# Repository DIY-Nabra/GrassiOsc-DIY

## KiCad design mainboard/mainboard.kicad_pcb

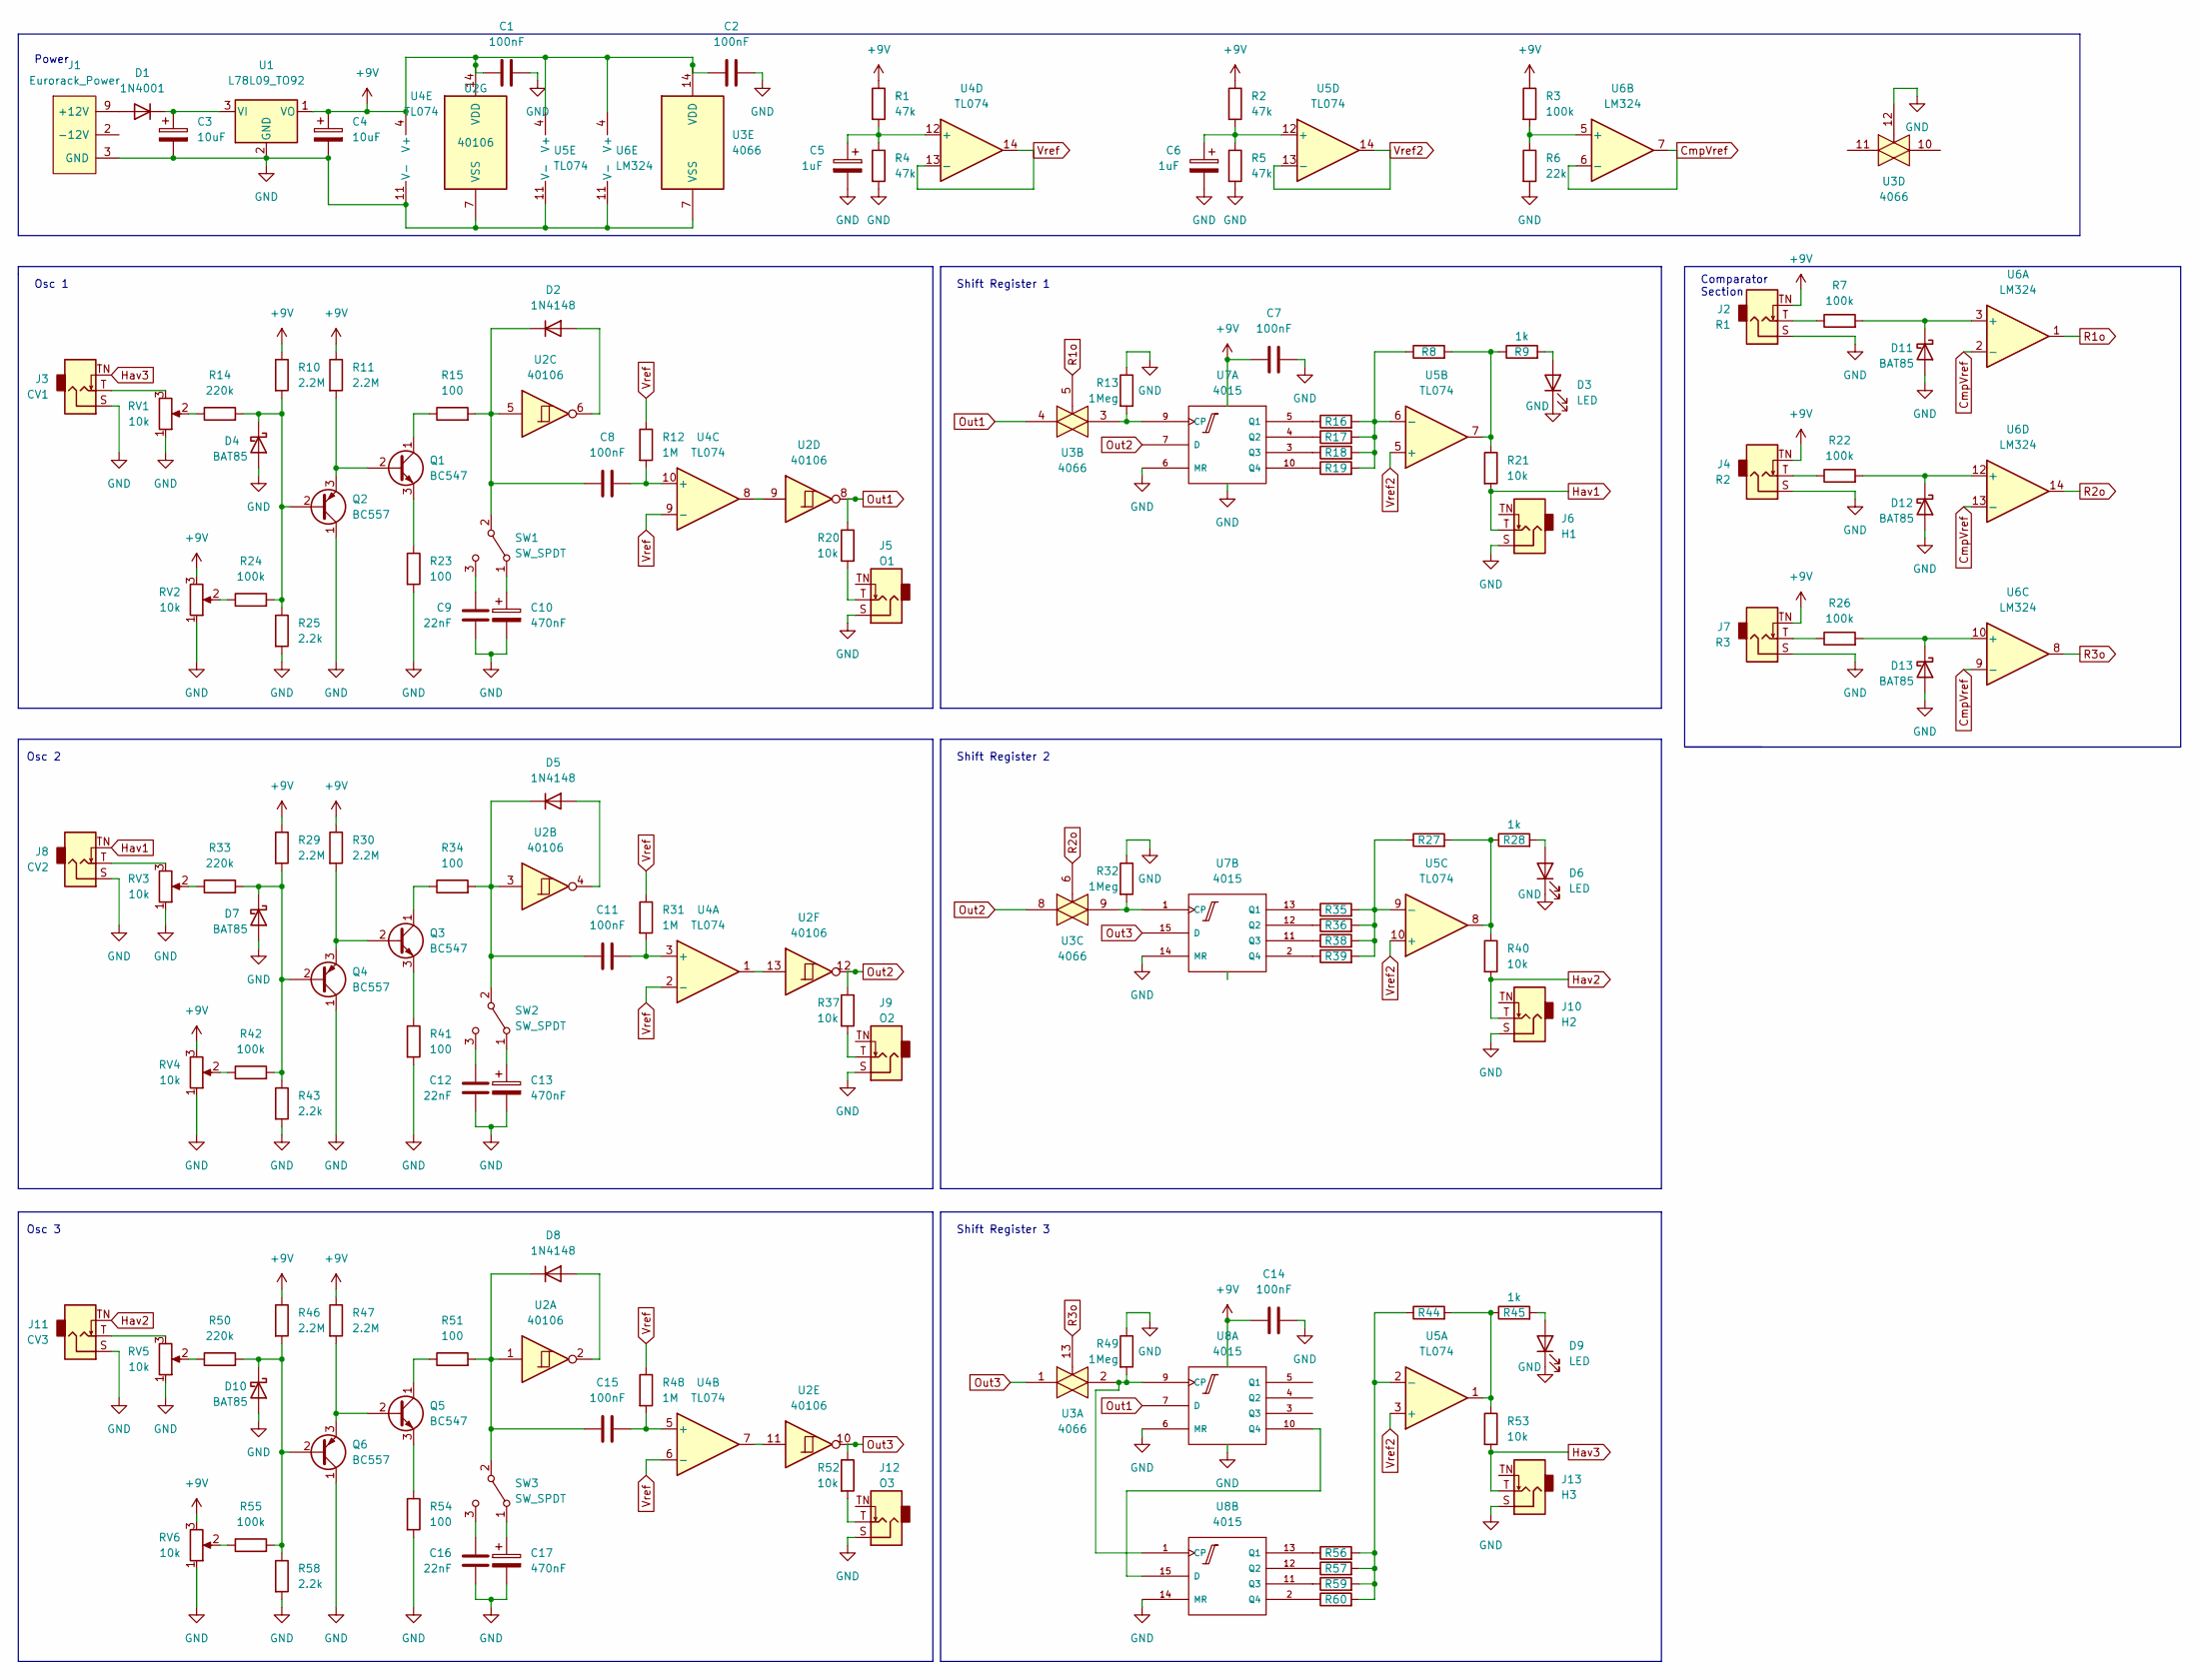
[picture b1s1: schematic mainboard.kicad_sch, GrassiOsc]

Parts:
C1, C2, C7, C14: 100nF; C_Disc_D5.0mm_W2.5mm_P2.50mm
C3, C4: 10uF; CP_Radial_D5.0mm_P2.50mm
C5, C6: 1uF; C_Disc_D3.8mm_W2.6mm_P2.50mm
C8, C11, C15: 100nF; C_Rect_L7.0mm_W2.5mm_P5.00mm
C9, C12, C16: 22nF; C_Disc_D5.0mm_W2.5mm_P2.50mm
C10, C13, C17: 470nF; CP_Radial_D5.0mm_P2.50mm
D1: 1N4001; D_DO-41_SOD81_P10.16mm_Horizontal
D2, D5, D8: 1N4148; D_DO-35_SOD27_P7.62mm_Horizontal
D3, D6, D9: LED; LED_D3.0mm
D4, D7, D10, D11, D12, D13: BAT85; D_DO-35_SOD27_P7.62mm_Horizontal
J1: Eurorack_Power; Eurorack_Power_2x5_Shrouded; mpn 302-S101
J2: R1; AudioJack_WQP518MA
J3: CV1; AudioJack_WQP518MA
J4: R2; AudioJack_WQP518MA
J5: O1; AudioJack_WQP518MA
J6: H1; AudioJack_WQP518MA
J7: R3; AudioJack_WQP518MA
J8: CV2; AudioJack_WQP518MA
J9: O2; AudioJack_WQP518MA
J10: H2; AudioJack_WQP518MA
J11: CV3; AudioJack_WQP518MA
J12: O3; AudioJack_WQP518MA
J13: H3; AudioJack_WQP518MA
Q1, Q3, Q5: BC547; TO-92_Inline
Q2, Q4, Q6: BC557; TO-92_Inline
R1, R2, R4, R5: 47k; R_Axial_DIN0204_L3.6mm_D1.6mm_P7.62mm_Horizontal
R3, R7, R22, R24, R26, R42, R55: 100k; R_Axial_DIN0204_L3.6mm_D1.6mm_P7.62mm_Horizontal
R6: 22k; R_Axial_DIN0204_L3.6mm_D1.6mm_P7.62mm_Horizontal
R8, R16, R17, R18, R19, R27, R35, R36, R38, R39, R44, R56, R57, R59, R60: R; R_Axial_DIN0204_L3.6mm_D1.6mm_P7.62mm_Horizontal
R9, R28, R45: 1k; R_Axial_DIN0204_L3.6mm_D1.6mm_P7.62mm_Horizontal
R10, R11, R29, R30, R46, R47: 2.2M; R_Axial_DIN0204_L3.6mm_D1.6mm_P7.62mm_Horizontal
R12, R31, R48: 1M; R_Axial_DIN0204_L3.6mm_D1.6mm_P7.62mm_Horizontal
R13, R32, R49: 1Meg; R_Axial_DIN0204_L3.6mm_D1.6mm_P7.62mm_Horizontal
R14, R33, R50: 220k; R_Axial_DIN0204_L3.6mm_D1.6mm_P7.62mm_Horizontal
R15, R23, R34, R41, R51, R54: 100; R_Axial_DIN0204_L3.6mm_D1.6mm_P7.62mm_Horizontal
R20, R21, R37, R40, R52, R53: 10k; R_Axial_DIN0204_L3.6mm_D1.6mm_P7.62mm_Horizontal
R25, R43, R58: 2.2k; R_Axial_DIN0204_L3.6mm_D1.6mm_P7.62mm_Horizontal
RV1, RV2, RV3, RV4, RV5, RV6: 10k; Potentiometer_Alpha_R0904N
SW1, SW2, SW3: SW_SPDT; Miniature_Switch_SPDT_2.54MM
U1: L78L09_TO92; TO-92_Inline
U2: 40106; DIP-14_W7.62mm_Socket
U3: 4066; DIP-14_W7.62mm_Socket
U4, U5: TL074; DIP-14_W7.62mm_Socket
U6: LM324; DIP-14_W7.62mm_Socket
U7, U8: 4015; DIP-16_W7.62mm_Socket

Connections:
+9V: C1.1, C2.1, C4.1, C7.1, C14.1, J2.TN, J4.TN, J7.TN, R1.1, R2.1, R3.1, R10.1, R11.1, R29.1, R30.1, R46.1, R47.1, RV2.3, RV4.3, RV6.3, U1.1 (VO), U2.14 (VDD), U3.14 (VDD), U4.4 (V+), U5.4 (V+), U6.4 (V+), U7.16 (Vdd), U8.16 (Vdd)
CmpVref: U6.2 (-), U6.6 (-), U6.7, U6.9 (-), U6.13 (-)
GND: C1.2, C2.2, C3.2, C4.2, C5.2, C6.2, C7.2, C9.1, C10.2, C12.1, C13.2, C14.2, C16.1, C17.2, D3.1 (K), D4.2 (A), D6.1 (K), D7.2 (A), D9.1 (K), D10.2 (A), D11.2 (A), D12.2 (A), D13.2 (A), J1.3 (GND), J1.4 (GND), J1.5 (GND), J1.6 (GND), J1.7 (GND), J1.8 (GND), J2.S, J3.S, J4.S, J5.S, J6.S, J7.S, J8.S, J9.S, J10.S, J11.S, J12.S, J13.S, Q2.1 (C), Q4.1 (C), Q6.1 (C), R4.2, R5.2, R6.2, R13.1, R23.2, R25.2, R32.1, R41.2, R43.2, R49.1, R54.2, R58.2, RV1.1, RV2.1, RV3.1, RV4.1, RV5.1, RV6.1, U1.2 (GND), U2.7 (VSS), U3.7 (VSS), U3.12, U4.11 (V-), U5.11 (V-), U6.11 (V-), U7.6 (MR), U7.8 (Vss), U7.14 (MR), U8.6 (MR), U8.8 (Vss), U8.14 (MR)
Hav1: J6.T, J8.TN, R21.2
Hav2: J10.T, J11.TN, R40.2
Hav3: J3.TN, J13.T, R53.2
unnamed: C3.1, D1.1 (K), U1.3 (VI)
unnamed: C5.1, R1.2, R4.1, U4.12 (+)
unnamed: C6.1, R2.2, R5.1, U5.12 (+)
unnamed: C8.1, D2.1 (K), R15.2, SW1.2 (B), U2.5
unnamed: C8.2, R12.2, U4.10 (+)
unnamed: C9.2, SW1.3 (C)
unnamed: C10.1, SW1.1 (A)
unnamed: C11.1, D5.1 (K), R34.2, SW2.2 (B), U2.3
unnamed: C11.2, R31.2, U4.3 (+)
unnamed: C12.2, SW2.3 (C)
unnamed: C13.1, SW2.1 (A)
unnamed: C15.1, D8.1 (K), R51.2, SW3.2 (B), U2.1
unnamed: C15.2, R48.2, U4.5 (+)
unnamed: C16.2, SW3.3 (C)
unnamed: C17.1, SW3.1 (A)
unnamed: D1.2 (A), J1.9 (+12V), J1.10 (+12V)
unnamed: D2.2 (A), U2.6
unnamed: D3.2 (A), R9.2
unnamed: D4.1 (K), Q2.2 (B), R10.2, R14.2, R24.2, R25.1
unnamed: D5.2 (A), U2.4
unnamed: D6.2 (A), R28.2
unnamed: D7.1 (K), Q4.2 (B), R29.2, R33.2, R42.2, R43.1
unnamed: D8.2 (A), U2.2
unnamed: D9.2 (A), R45.2
unnamed: D10.1 (K), Q6.2 (B), R46.2, R50.2, R55.2, R58.1
unnamed: D11.1 (K), R7.2, U6.3 (+)
unnamed: D12.1 (K), R22.2, U6.12 (+)
unnamed: D13.1 (K), R26.2, U6.10 (+)
unnamed: J1.1 (-12V), J1.2 (-12V)
unnamed: J2.T, R7.1
unnamed: J3.T, RV1.3
unnamed: J4.T, R22.1
unnamed: J5.T, R20.2
unnamed: J7.T, R26.1
unnamed: J8.T, RV3.3
unnamed: J9.T, R37.2
unnamed: J11.T, RV5.3
unnamed: J12.T, R52.2
unnamed: Q1.1 (C), R15.1
unnamed: Q1.2 (B), Q2.3 (E), R11.2
unnamed: Q1.3 (E), R23.1
unnamed: Q3.1 (C), R34.1
unnamed: Q3.2 (B), Q4.3 (E), R30.2
unnamed: Q3.3 (E), R41.1
unnamed: Q5.1 (C), R51.1
unnamed: Q5.2 (B), Q6.3 (E), R47.2
unnamed: Q5.3 (E), R54.1
unnamed: R3.2, R6.1, U6.5 (+)
unnamed: R13.2, U3.3, U7.9 (CP)
unnamed: R14.1, RV1.2
unnamed: R16.1, U7.5 (Q1)
unnamed: R8.1, R16.2, R17.2, R18.2, R19.2, U5.6 (-)
unnamed: R17.1, U7.4 (Q2)
unnamed: R18.1, U7.3 (Q3)
unnamed: R19.1, U7.10 (Q4)
unnamed: R8.2, R9.1, R21.1, U5.7
unnamed: R24.1, RV2.2
unnamed: R27.1, R35.2, R36.2, R38.2, R39.2, U5.9 (-)
unnamed: R27.2, R28.1, R40.1, U5.8
unnamed: R32.2, U3.9, U7.1 (CP)
unnamed: R33.1, RV3.2
unnamed: R35.1, U7.13 (Q1)
unnamed: R36.1, U7.12 (Q2)
unnamed: R38.1, U7.11 (Q3)
unnamed: R39.1, U7.2 (Q4)
unnamed: R42.1, RV4.2
unnamed: R44.1, R56.2, R57.2, R59.2, R60.2, U5.2 (-)
unnamed: R44.2, R45.1, R53.1, U5.1
unnamed: R49.2, U3.2, U8.1 (CP), U8.9 (CP)
unnamed: R50.1, RV5.2
unnamed: R55.1, RV6.2
unnamed: R56.1, U8.13 (Q1)
unnamed: R57.1, U8.12 (Q2)
unnamed: R59.1, U8.11 (Q3)
unnamed: R60.1, U8.2 (Q4)
unnamed: U2.9, U4.8
unnamed: U2.11, U4.7
unnamed: U2.13, U4.1
unnamed: U8.10 (Q4), U8.15 (D)
Out1: R20.1, U2.8, U3.4, U8.7 (D)
Out2: R37.1, U2.12, U3.8, U7.7 (D)
Out3: R52.1, U2.10, U3.1, U7.15 (D)
R1o: U3.5, U6.1
R2o: U3.6, U6.14
R3o: U3.13, U6.8
Vref: R12.1, R31.1, R48.1, U4.2 (-), U4.6 (-), U4.9 (-), U4.13 (-), U4.14
Vref2: U5.3 (+), U5.5 (+), U5.10 (+), U5.13 (-), U5.14

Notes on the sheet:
Osc 3
Shift Register 3
Osc 1
Shift Register 1
Osc 2
Shift Register 2
Comparator Section
Power

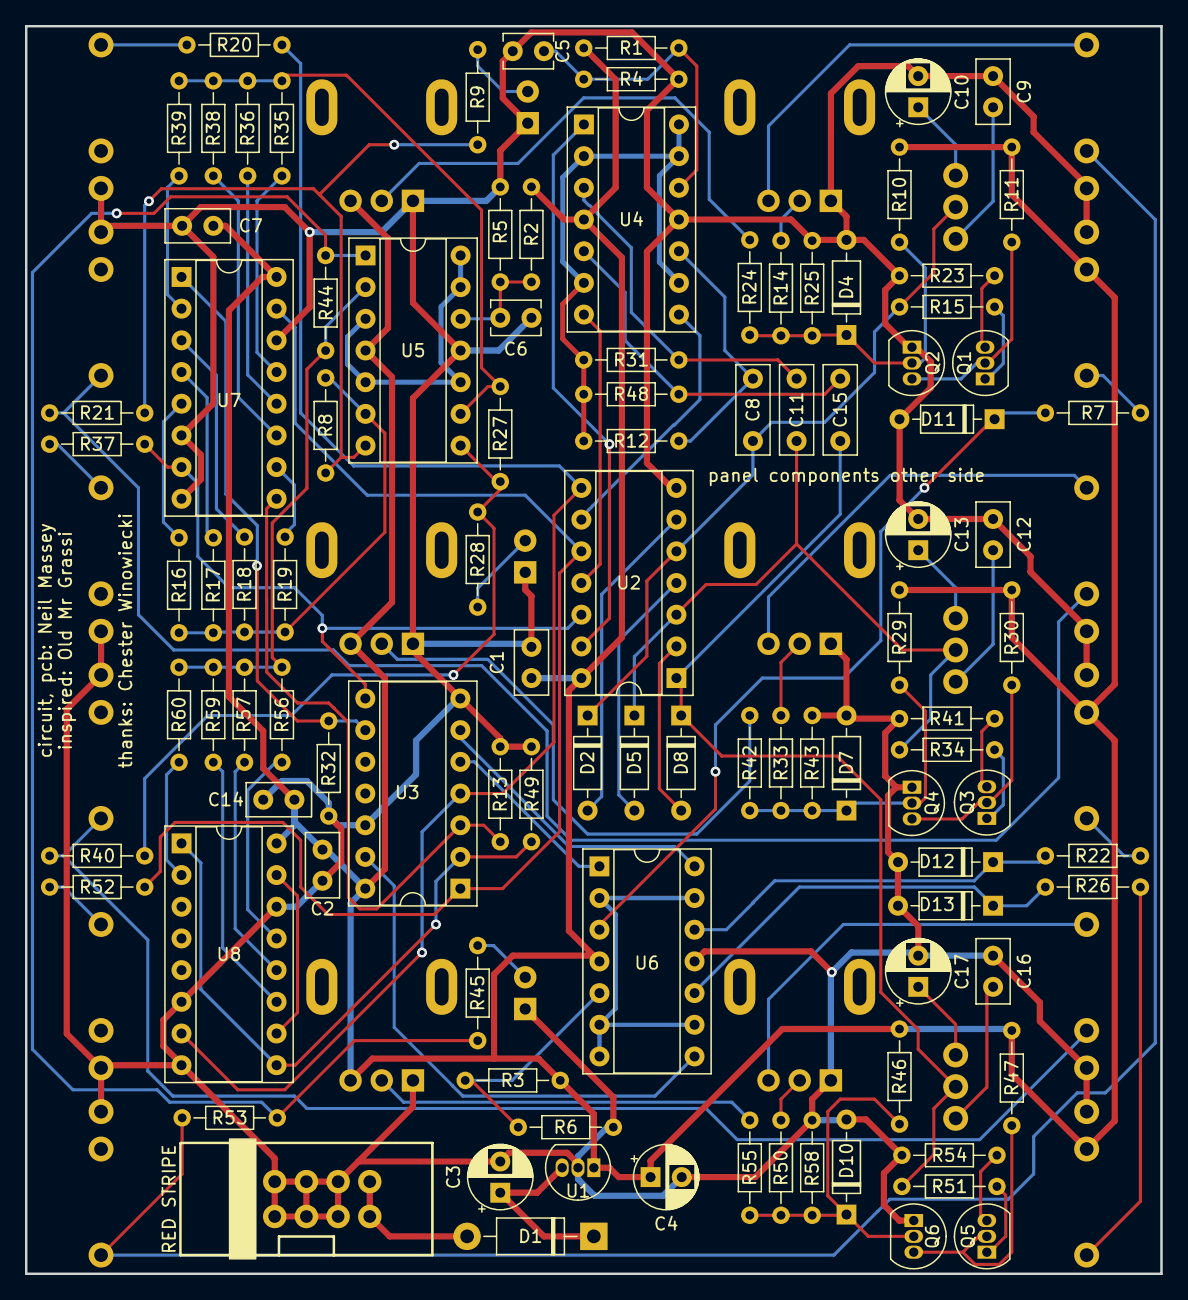
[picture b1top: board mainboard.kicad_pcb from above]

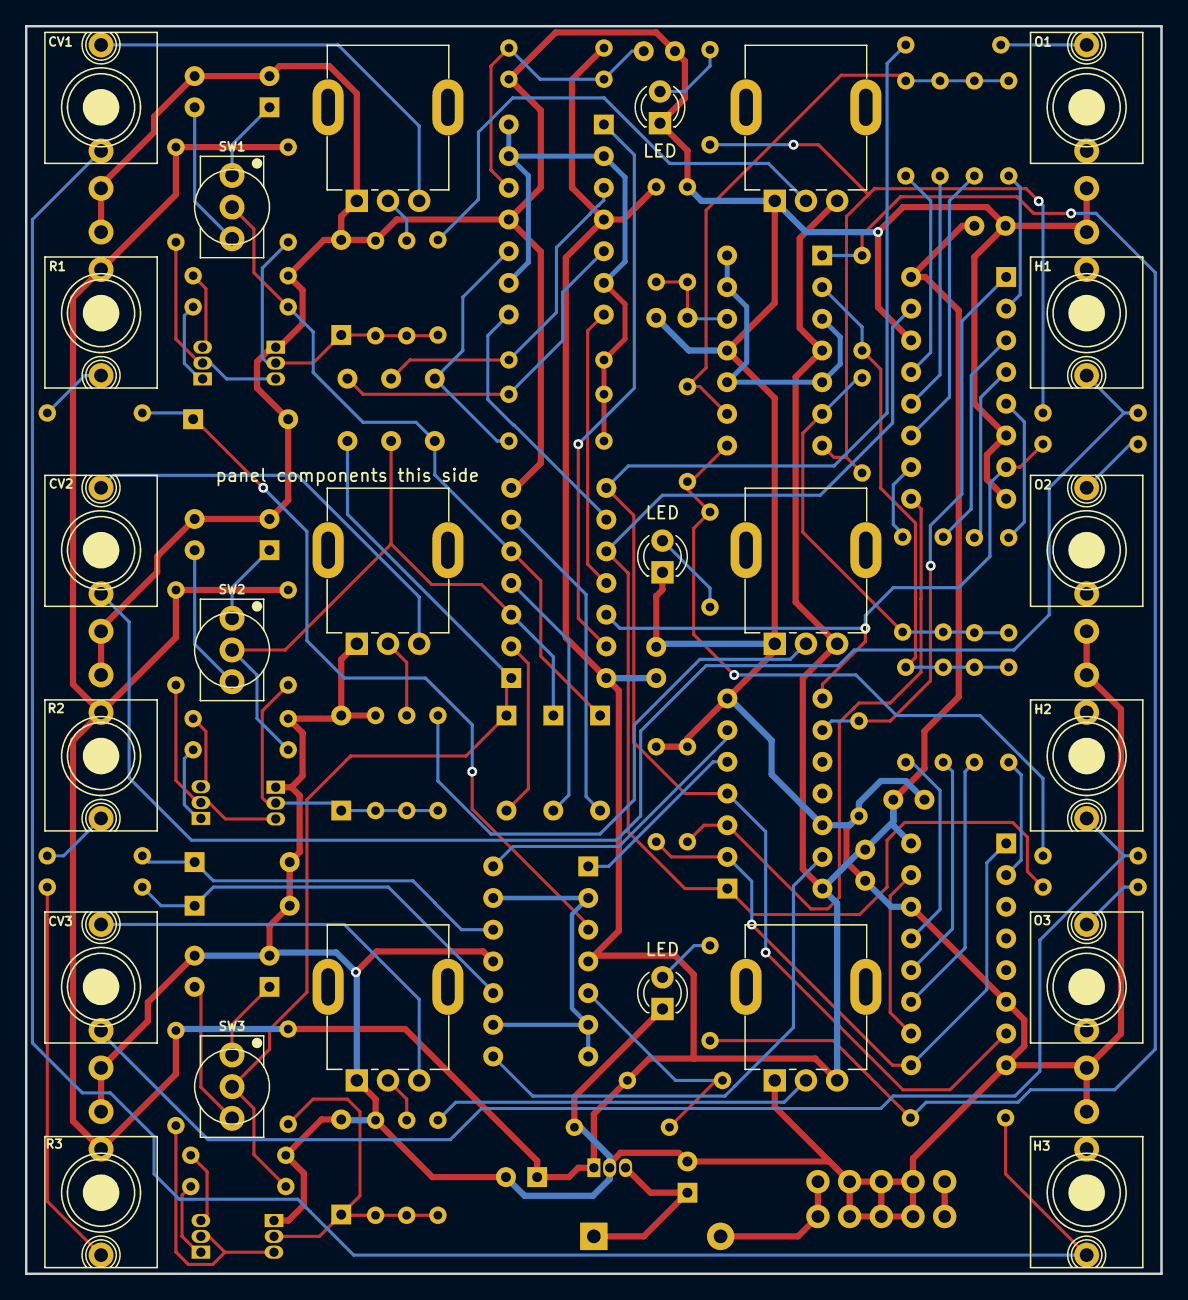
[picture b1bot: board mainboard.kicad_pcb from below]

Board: 2 copper layers, 91.0 x 100.0 mm, 126 parts (24 on the bottom side), 93 nets.

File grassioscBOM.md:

# GrassiOsc Bill of Materials (BOM)

To build just follow the order in the BOM.

When soldering the ICs (U2->U8), solder in the equivalent sockets instead.

Solder the panel components (jacks and pots) last, on the opposite side of the board to the other parts.

| Reference				| Quantity	| Part	| Notes |
| --------------------------------------- | -------------- | ------- | -------- |
| R15,R23,R34,R41,R51,R54			|6	| 100R	| |
| R9,R28,R45				|3	| 1k	| LED protection resistors |
| R20,R21,R37,R40,R52,R53			|6	| 1k or 10k	| Output resistors |
| R3,R7,R22,R24,R26,R42,R55		|7	| 100k	| |
| R12,R13,R31,R32,R48,R49			|3	| 1M	| |
| R25,R43,R58				|3	| 2.2k	| |
| R6					|1	| 22k	| |
| R14,R33,R50				|3	| 220k	| |
| R10,R11,R29,R30,R46,R47			|6	| 2.2M	| |
| R1,R2,R4,R5				|4	| 47k	| |
| R16,R17,R18,R19,R35,R36,R38,R39,R56,R57,R59,R60	| 12	| Choose your own (see build note)	| DAC resistors |
| R8,R27,R44				|3	| Choose your own (see build note)	| DAC amplifier resistors |
| D1					|1	| 1N4001	| Reverse polarity protection diode |
| D3,D6,D9				|3	| 3mm LED	| Standard brightness |
| D2,D5,D8				|3 	| 1N4148	 | |
| D4,D7,D10,D11,D12,D13			|6	| BAT85	| Negative voltage protection diodes |
| Q1,Q3,Q5				|3	| BC547 TO92	 | |
| Q2,Q4,Q6				|3	| BC557 TO92	 | |
| C3,C4					|2	| 10uF electrolytic	| Power conditioning caps |
| C8,C11,C15				|3	| 100nF mylar	| Oscillator AC coupling cap.  Can substitute MLCC |
| C10,C13,C17				|3	| 470nF electrolytic	| Oscillator timing cap: control rate |
| C5,C6					|2	| 1uF electrolytic	| MIDO voltage conditioning cap.  Can substitute MLCC |
| C1,C2,C7,C14				|4	| 100nF ceramic disc	| IC decoupling capacitors |
| C9,C12,C16				|3	| 22nF mylar	| Oscillator timing cap: audio rate |
| U1					|1	| L78L09 TO92	| Power regulator |
| U2					|1	| CD40106	| |
| U3					|1	| CD4066	 | |
| U4,U5					|2	| TL074	| Or TL084 | |
| U6					|1	| LM324	| DO NOT use TL074 or TL084 | |
| U7,U8					|2	| CD4015	| |
| SW1,SW2,SW3				|3	| SPDT miniature switch 2.54mm pitch |
| RV1,RV2,RV3,RV4,RV5,RV6			|6	| 10k 9mm potentiometer |
| J1					|1	| Eurorack 2x5 shrouded male |
| J2,J3,J4,J5,J6,J7,J8,J9,J10,J11,J12,J13	|12	| Thonkiconn 3.5mm mono socket |
| IC socket 14 pin	DIP-14_W7.62mm_Socket	|5	| DIP 14 pin socket |
| IC socket 16 pin	DIP-16_W7.62mm_Socket	|2	| DIP 16 pin socket |

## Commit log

2022-08-03 First commit of panel
2022-08-04 Some more routing, moved D2, D5 and D8 to make it cleanr
2022-08-15 Routing
2022-08-18 Panel commit
2022-08-25 Traces corrected
2022-08-26 Panel tweak
2022-08-26 Panel tweaks
2022-08-26 Added LICENSE
2022-08-26 Added BOM
2022-08-26 Amended BOM
2022-08-27 nologo panel and branch
2022-09-03 updated BOM
2022-09-11 Rerouted: number of vias reduced from 39 to 13
